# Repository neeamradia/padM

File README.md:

# padM
Macro-Pad customised for myself.

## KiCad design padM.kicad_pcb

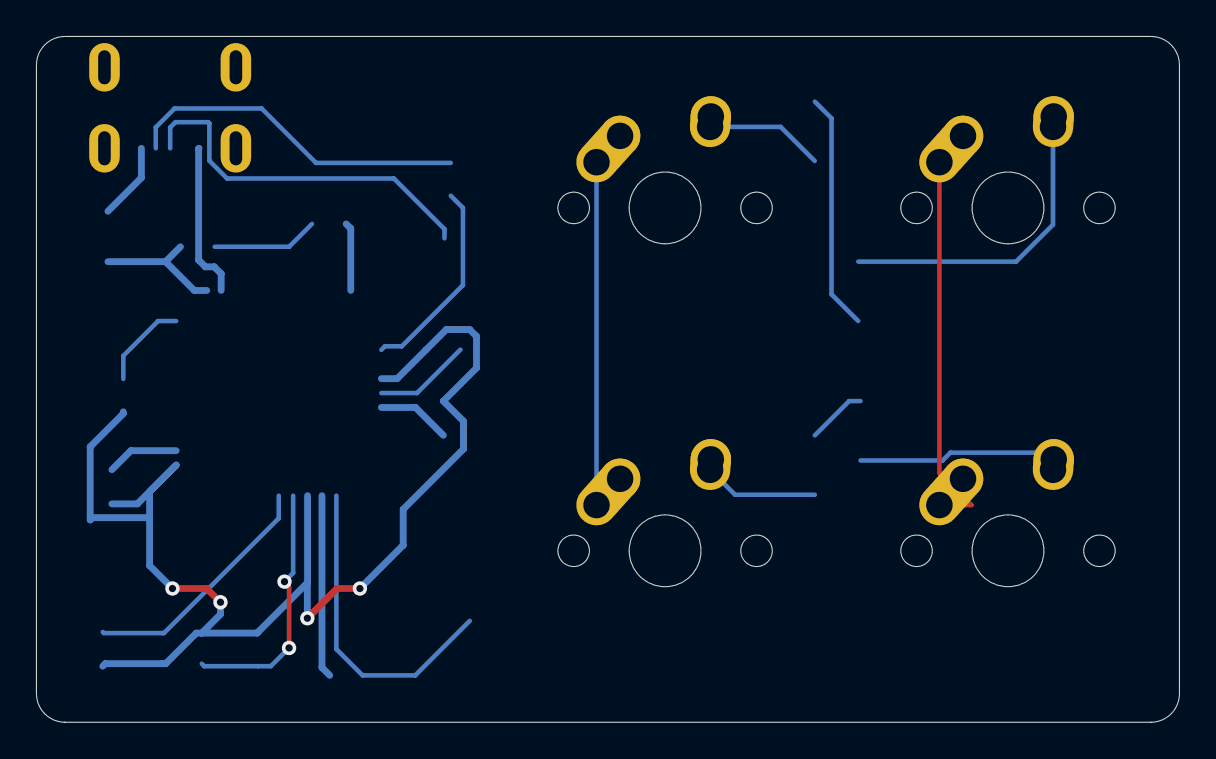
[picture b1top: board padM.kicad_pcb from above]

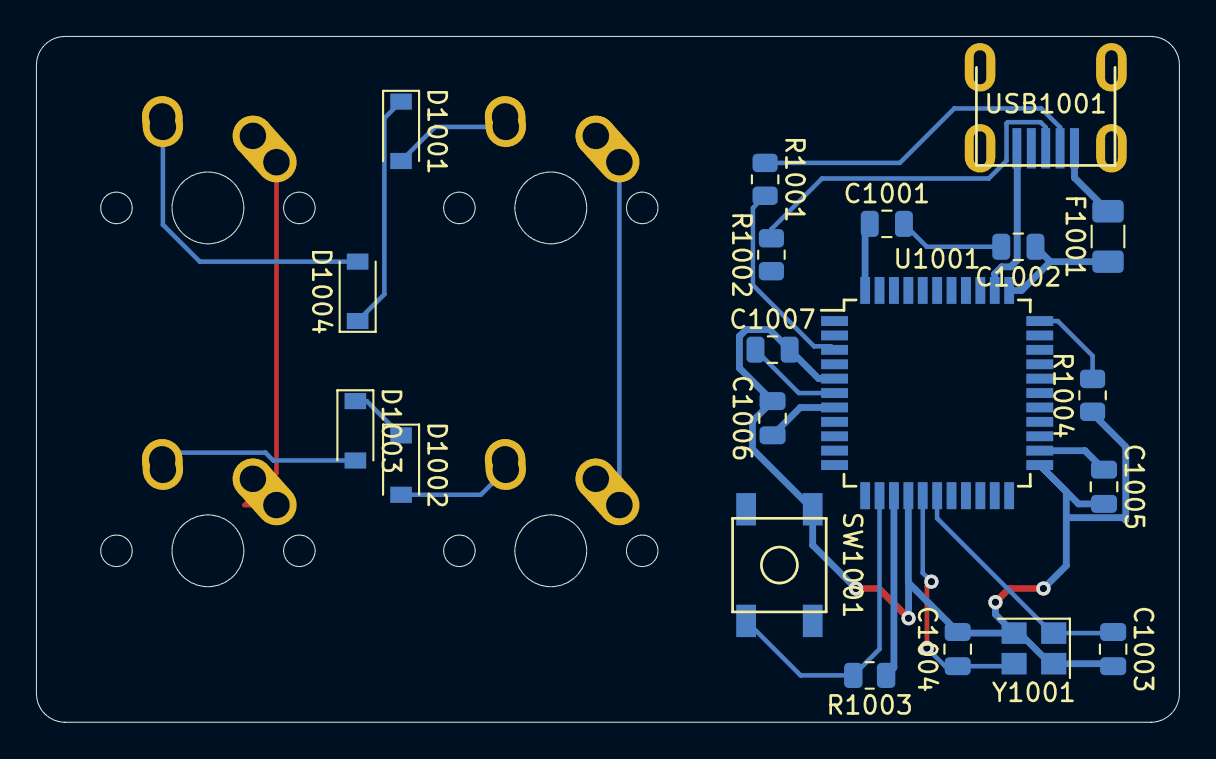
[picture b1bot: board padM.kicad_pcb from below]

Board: 2 copper layers, 63.5 x 38.1 mm, 24 parts (20 on the bottom side), 21 nets.

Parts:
C1001: 10uf; C_0805_2012Metric
C1002, C1005, C1006: 0.1uF; C_0805_2012Metric
C1003, C1004: 22pF; C_0805_2012Metric
C1007: 1uF; C_0805_2012Metric
D1001, D1002, D1003, D1004: D_Small; D_SOD-123
F1001: 500mA; Fuse_1206_3216Metric
MX1001, MX1002, MX1003, MX1004: MX-NoLED; MX-1U-NoLED
R1001, R1002: 22; R_0805_2012Metric
R1003, R1004: 10k; R_0805_2012Metric
SW1001: SW_Push; SKQG-1155865
U1001: ATmega32U4-AU; TQFP-44_10x10mm_P0.8mm
USB1001: Molex-0548190589
Y1001: 16MHz; Crystal_SMD_3225-4Pin_3.2x2.5mm

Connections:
+5V: C1001.1, C1002.1, C1005.1, C1006.1, F1001.1, R1003.1, U1001.2, U1001.7, U1001.14, U1001.24, U1001.34, U1001.44
COL1: MX1003.1, MX1004.1
D+: R1002.2, USB1001.3
D-: R1001.1, USB1001.4
GND: C1003.2, C1004.2, C1005.2, C1006.2, C1007.2, R1004.1, SW1001.1, U1001.5, U1001.15, U1001.23, U1001.35, U1001.43, USB1001.1, Y1001.2, Y1001.4
unnamed: C1001.2, C1002.2
unnamed: C1003.1, U1001.17, Y1001.1
unnamed: C1004.1, U1001.16, Y1001.3
unnamed: C1007.1, U1001.6
unnamed: D1001.2, MX1001.2
unnamed: D1002.2, MX1002.2
unnamed: D1003.2, MX1003.2
unnamed: D1004.2, MX1004.2
unnamed: MX1001.1, MX1002.1
unnamed: R1001.2, U1001.3
unnamed: R1002.1, U1001.4
unnamed: R1003.2, SW1001.2, U1001.13
unnamed: R1004.2, U1001.33
ROW0: D1001.1, D1004.1
ROW1: D1002.1, D1003.1
VCC: F1001.2, USB1001.5

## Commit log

2023-06-20 Add submodules
2023-06-20 added kicad files
2023-06-20 good
2023-06-22 footprinted
2023-06-22 kicad work
2023-06-22 add subm
